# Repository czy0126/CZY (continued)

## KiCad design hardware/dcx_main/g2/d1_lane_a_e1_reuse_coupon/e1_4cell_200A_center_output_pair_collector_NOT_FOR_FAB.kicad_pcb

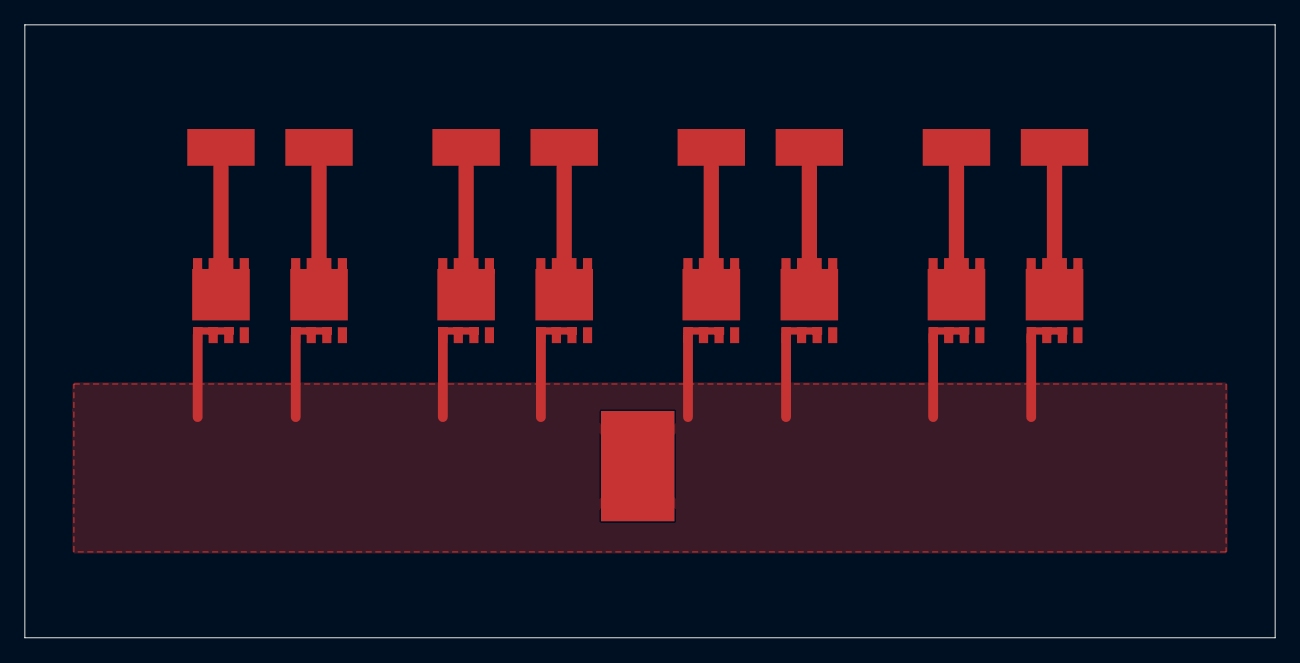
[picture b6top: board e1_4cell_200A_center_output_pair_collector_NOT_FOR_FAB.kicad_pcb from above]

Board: 12 copper layers, 102.0 x 50.0 mm, 22 parts (0 on the bottom side), 10 nets.

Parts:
CTAP_1, CTAP_2, CTAP_3, CTAP_4: E1_POWER_LAND_UNRATED_COUPON_NO_ACTIVE_WINDING
IN_1A, IN_1B, IN_2A, IN_2B, IN_3A, IN_3B, IN_4A, IN_4B: E1_POWER_LAND_UNRATED_COUPON_NO_ACTIVE_WINDING
OUT_NEG: E1_POWER_LAND_UNRATED_COUPON_NO_ACTIVE_WINDING
OUT_POS: E1_POWER_LAND_UNRATED_COUPON_NO_ACTIVE_WINDING
SR1A, SR1B, SR2A, SR2B, SR3A, SR3B, SR4A, SR4B: V17_SR_FOOTPRINT_REUSED_UNRATED_NOT_FOR_FAB

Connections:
PGND: OUT_NEG.1, SR1A.1, SR1A.2, SR1A.3, SR1B.1, SR1B.2, SR1B.3, SR2A.1, SR2A.2, SR2A.3, SR2B.1, SR2B.2, SR2B.3, SR3A.1, SR3A.2, SR3A.3, SR3B.1, SR3B.2, SR3B.3, SR4A.1, SR4A.2, SR4A.3, SR4B.1, SR4B.2, SR4B.3
SEC1_A: IN_1A.1, SR1A.5, SR1A.6, SR1A.7, SR1A.8
SEC1_B: IN_1B.1, SR1B.5, SR1B.6, SR1B.7, SR1B.8
SEC2_A: IN_2A.1, SR2A.5, SR2A.6, SR2A.7, SR2A.8
SEC2_B: IN_2B.1, SR2B.5, SR2B.6, SR2B.7, SR2B.8
SEC3_A: IN_3A.1, SR3A.5, SR3A.6, SR3A.7, SR3A.8
SEC3_B: IN_3B.1, SR3B.5, SR3B.6, SR3B.7, SR3B.8
SEC4_A: IN_4A.1, SR4A.5, SR4A.6, SR4A.7, SR4A.8
SEC4_B: IN_4B.1, SR4B.5, SR4B.6, SR4B.7, SR4B.8
VOUT: CTAP_1.1, CTAP_2.1, CTAP_3.1, CTAP_4.1, OUT_POS.1

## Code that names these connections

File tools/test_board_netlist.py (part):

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
def test_high_side_fets_are_wired_across_the_input(netlist):
    _, rows, _ = netlist
    assert pins_of(rows, "QH") == {"D": "VIN_P", "S": "SW", "G": "GH"}
    assert pins_of(rows, "QL") == {"D": "SW", "S": "PGND", "G": "GL"}


def test_the_cavity_is_cr_then_ct_then_lr(netlist):
    """sw -Cr- CR_CT -CT- CT_LR -Lr- primary, exactly as the deck chains them."""
    _, rows, _ = netlist
    assert pins_of(rows, "Cr") == {"N1": "SW", "N2": "CR_CT"}
    assert pins_of(rows, "CT") == {"PRI_A": "CR_CT", "PRI_B": "CT_LR",
                                   "SEC_A": "CS1", "SEC_B": "CS2"}
    assert pins_of(rows, "Lr") == {"N1": "CT_LR", "N2": "PRI_T1"}


def test_the_four_primaries_are_in_series_and_end_at_pgnd(netlist):
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    for i in (1, 2, 3, 4):
        pins = pins_of(rows, f"T{i}")
        assert len(pins) == 5, pins
        assert pins["CTAP"] == "VOUT"
        assert pins["SEC_A"] == f"SEC{i}_A"
        assert pins["SEC_B"] == f"SEC{i}_B"


def test_synchronous_rectifiers_go_from_secondary_to_pgnd(netlist):
    _, rows, _ = netlist
    for i in (1, 2, 3, 4):
        assert pins_of(rows, f"SR{i}A") == {"D": f"SEC{i}_A", "G": f"GA{i}", "S": "PGND"}
        assert pins_of(rows, f"SR{i}B") == {"D": f"SEC{i}_B", "G": f"GB{i}", "S": "PGND"}


def test_u1_pin_numbers_match_the_verified_map(netlist):
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def test_the_sr_controllers_carry_their_own_reg_caps(netlist):
    _, rows, _ = netlist
    for i, n in enumerate((3, 4, 5, 6), start=1):
        assert pins_of(rows, f"U{n}")["3"] == f"REG{i}"
        assert net_refs(rows, f"REG{i}") == [f"C{n + 4}", f"U{n}"]


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    for i in (1, 2, 3, 4):
        transformer = report["transformers"][f"T{i}"]
        a, b = transformer["secondary_a"], transformer["secondary_b"]
        assert (a["dot_pin"], a["non_dot_pin"]) == ("CTAP", "SEC_A")
        assert (b["dot_pin"], b["non_dot_pin"]) == ("SEC_B", "CTAP")
        assert a["dot_node"] == b["non_dot_node"] == "out"
        assert a["non_dot_node"] == f"a{i}"
        assert b["dot_node"] == f"b{i}"
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
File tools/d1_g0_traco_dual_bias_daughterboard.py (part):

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# KiCad Python: .../KiCad/10.0/bin/python.exe -> .../KiCad/10.0/share/kicad/footprints
FOOTLIB=Path(sys.executable).parents[1]/"share/kicad/footprints"
TRACO="Converter_DCDC_TRACO_THN30-xxxx_THT"
PINS={"1":"+Vin","2":"-Vin","3":"+Vout","4":"Trim","5":"-Vout","6":"Remote"}
NETS=("VIN48_PRE","PGND","VIN48P_F","VIN48S_F","VCC12","VCC12_S","SR_SOURCE_RETURN")
MPN="THN 30-4812"
FUSE_VALUE="2A_SLOW_75VDC_MIN_Q_DFMR_REQUIRED"
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 "connector":("TerminalBlock","TerminalBlock_MaiXu_MX126-5.0-02P_1x02_P5.00mm")
}
PARTS={
 "J_IN": {"type":"connector","position":(9.,13.),"value":"INPUT_48V_PRE_EST0P","pins":{"1":"VIN48_PRE","2":"PGND"}},
 "F1": {"type":"fuse","position":(28.,9.),"value":FUSE_VALUE,"pins":{"1":"VIN48_PRE","2":"VIN48P_F"}},
 "F2": {"type":"fuse","position":(79.,9.),"value":FUSE_VALUE,"pins":{"1":"VIN48_PRE","2":"VIN48S_F"}},
 "U1": {"type":"module","position":(33.,18.),"value":MPN,
        "pins":{"1":"VIN48P_F","2":"PGND","3":"VCC12","4":"","5":"PGND","6":""}},
 "U2": {"type":"module","position":(84.,18.),"value":MPN,
        "pins":{"1":"VIN48S_F","2":"PGND","3":"VCC12_S","4":"","5":"SR_SOURCE_RETURN","6":""}},
 "C_INP":{"type":"input_cap","position":(43.,10.),"value":CAP_IN_VALUE,
         "pins":{"1":"VIN48P_F","2":"PGND"}},
 "C_INS":{"type":"input_cap","position":(94.,10.),"value":CAP_IN_VALUE,
         "pins":{"1":"VIN48S_F","2":"PGND"}},
 "C_P1":{"type":"output_cap","position":(25.,51.),"value":CAP_OUT_VALUE,
         "pins":{"1":"VCC12","2":"PGND"}},
 "C_P2":{"type":"output_cap","position":(42.,51.),"value":CAP_OUT_VALUE,
         "pins":{"1":"VCC12","2":"PGND"}},
 "C_S1":{"type":"output_cap","position":(76.,51.),"value":CAP_OUT_VALUE,
         "pins":{"1":"VCC12_S","2":"SR_SOURCE_RETURN"}},
 "C_S2":{"type":"output_cap","position":(94.,51.),"value":CAP_OUT_VALUE,
         "pins":{"1":"VCC12_S","2":"SR_SOURCE_RETURN"}},
 "J_P":{"type":"connector","position":(30.,63.),"value":"PRIMARY_12V_OUT",
        "pins":{"1":"VCC12","2":"PGND"}},
 "J_S":{"type":"connector","position":(81.,63.),"value":"SECONDARY_12V_OUT",
        "pins":{"1":"VCC12_S","2":"SR_SOURCE_RETURN"}},
}
BOARD_W=115.
BOARD_H=75.
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        physical[ref]=got
    for ref in ("U1","U2"):
        pin=physical[ref]
        if pin["2"]!="PGND" or pin["6"] or pin["4"]:
            raise ValueError("two module remote/trim must stay NC")
    if physical["U2"]["5"]!="SR_SOURCE_RETURN" or physical["U1"]["5"]!="PGND":
        raise ValueError("48V Traco isolated secondary output bonded to input ground")
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
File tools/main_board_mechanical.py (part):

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SOIC8_W, SOIC8_D, SOIC8_H = 7.4, 5.4, 1.75
# The REG crowbar (doc 34, package C: "紧接着连接选定的实际硬件关断电路").  Not a
# new circuit: it is the shutdown `pcb/sr_fault_validation` selected, with one
# copy per controller.  UCC24624 has no enable pin -- only a REG undervoltage or
# standby pulls VG low -- so pulling REG through 4.7 ohm (12.1 us) is the chosen
# route, against 75.5 ms for cutting VDD.
#
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    # 34, package C: "紧接着连接选定的实际硬件关断电路").  Placing U3-U6 needs no
    # ECO: the golden netlist, the BOM row "U3-U6" and theme section 3 already
    # carry them; what was missing was a pad to land on.  With them placed, each
    # VD*/VG* becomes a two-pad net and REG1-REG4 appear as the pin the REG
    # crowbar will pull.
    for i, x0 in enumerate(SR_X0, start=1):
        out.append(Part(f"U{i + 2}", "UCC24624DR", SOIC8_W, SOIC8_D, SOIC8_H,
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                        "kicad-library", SOIC8_FP,
                        note=f"dual SR controller for group {i}: pin 1/8 drive VG{i}_A/B "
                             f"through R{20 + 2 * (i - 1)}/R{21 + 2 * (i - 1)}, pin 4/6 "
                             f"sit on the drain Kelvin links, pin 3 (REG{i}) is the "
                             f"node a crowbar pulls, pin 7 is VCC12_S.  MPN from "
                             f"bom_draft.csv U3-U6 (ucc24624.pdf); land is the "
                             f"vendored KiCad SOIC-8, not a vendor drawing"))
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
